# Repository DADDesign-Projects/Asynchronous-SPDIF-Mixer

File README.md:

# Asynchronous S/PDIF Mixer

"Asynchronous SPDIF Mixer" is a hardware and software project designed to synchronize and mix up to three asynchronous S/PDIF streams into a single 48 kHz output stream.  
The system compensates for drift between sources and uses interpolation to ensure smooth and artifact-free audio transitions.  
The project includes USB-MIDI control, allowing real-time mixing of the three audio channels via an external MIDI controller or any MIDI-compatible software.
  
The software, developed in C++ with CubeIDE, is optimized for real-time audio processing and runs on an STM32H743 microcontroller.  
A custom electronic board, designed with KiCad, provides a dedicated hardware platform for this solution.  

## 📋 New Evolutions

Recent updates to the project include:

- 🔄 **Enhanced Drift Compensation**: A new algorithm has been implemented for compensating drifts in the input frequencies, ensuring more precise synchronization across streams.
- 🎛️ **Advanced Mixing Controls**: Mixing between the three inputs can now be adjusted in real-time via MIDI over USB, complemented by a Python-based control panel for intuitive configuration. Mix settings are automatically saved and recalled as presets stored directly in flash memory for persistent, non-volatile access.

## 👤 Author

This project is developed by **DAD Design**.

## 📄 License

This project is licensed under the [MIT License](LICENSE).

## ✨ Features

- **Synchronization of Asynchronous S/PDIF Streams:** The project synchronizes three input audio streams, each potentially running at different sample rates ( 48kHz, 44.1kHz, 32kHz), into a unified output stream at 48kHz.
- **Clock Drift Compensation:** Drift between the input streams is handled through periodic drift factor recalculation, ensuring the output remains smooth and synchronized.
- 🎛️ **Real-Time Mixing Controls**: Adjustable mixing levels for the three inputs via any USB-MIDI interface. A Python control panel included as an example for easy configuration.
- 💾 **Preset Memorization**: Mix settings are automatically saved and can be recalled as presets stored in flash memory for quick, persistent access.

## 🛠️ Hardware Platform

The KiCAD folder contains the schematics and PCB files for the project's hardware. These files were created using **KiCAD version 9.0**.

## 🔧 Development Environment

The project is developed and compiled using the **CubeIDE** environment provided by STMicroelectronics. CubeIDE is a fully integrated development environment (IDE) that supports STM32 microcontrollers and provides tools for debugging, flashing, and developing embedded systems.

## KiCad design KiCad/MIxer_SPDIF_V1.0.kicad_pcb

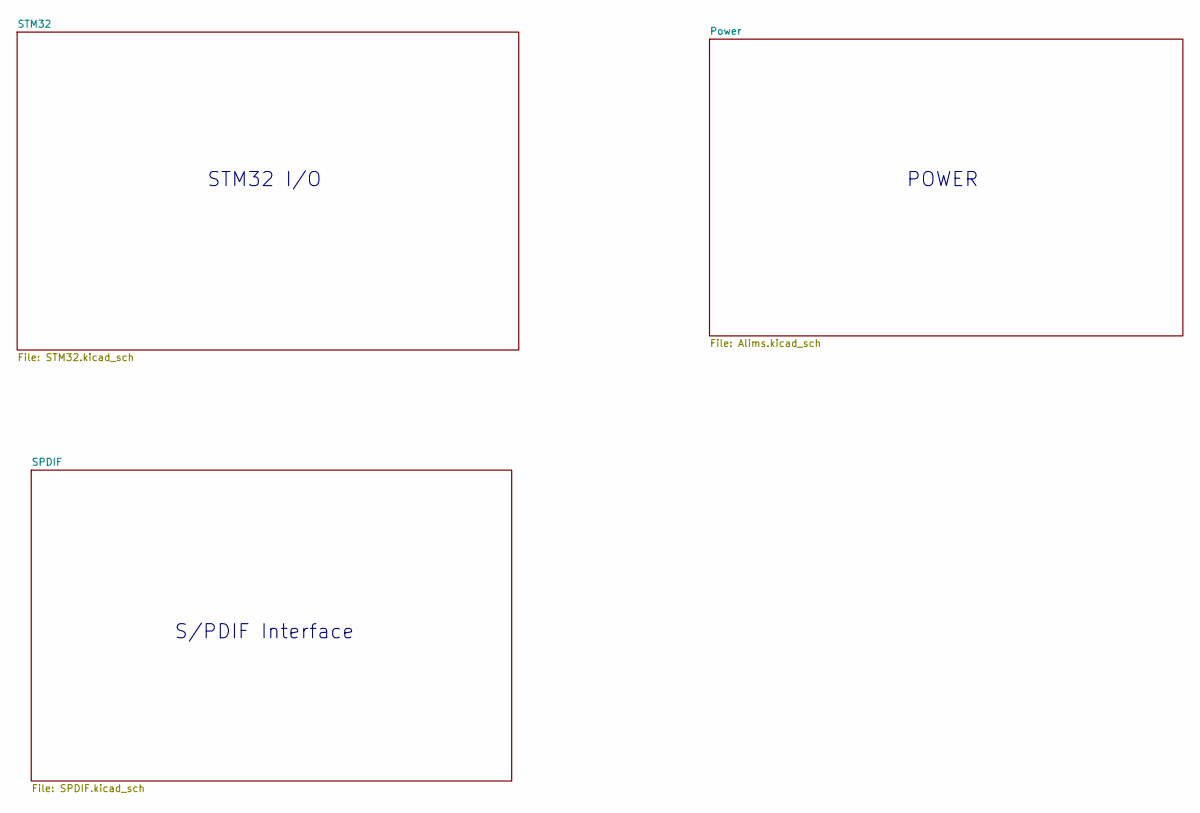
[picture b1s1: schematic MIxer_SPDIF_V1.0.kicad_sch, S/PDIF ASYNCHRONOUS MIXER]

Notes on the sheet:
POWER
S/PDIF Interface
STM32 I/O

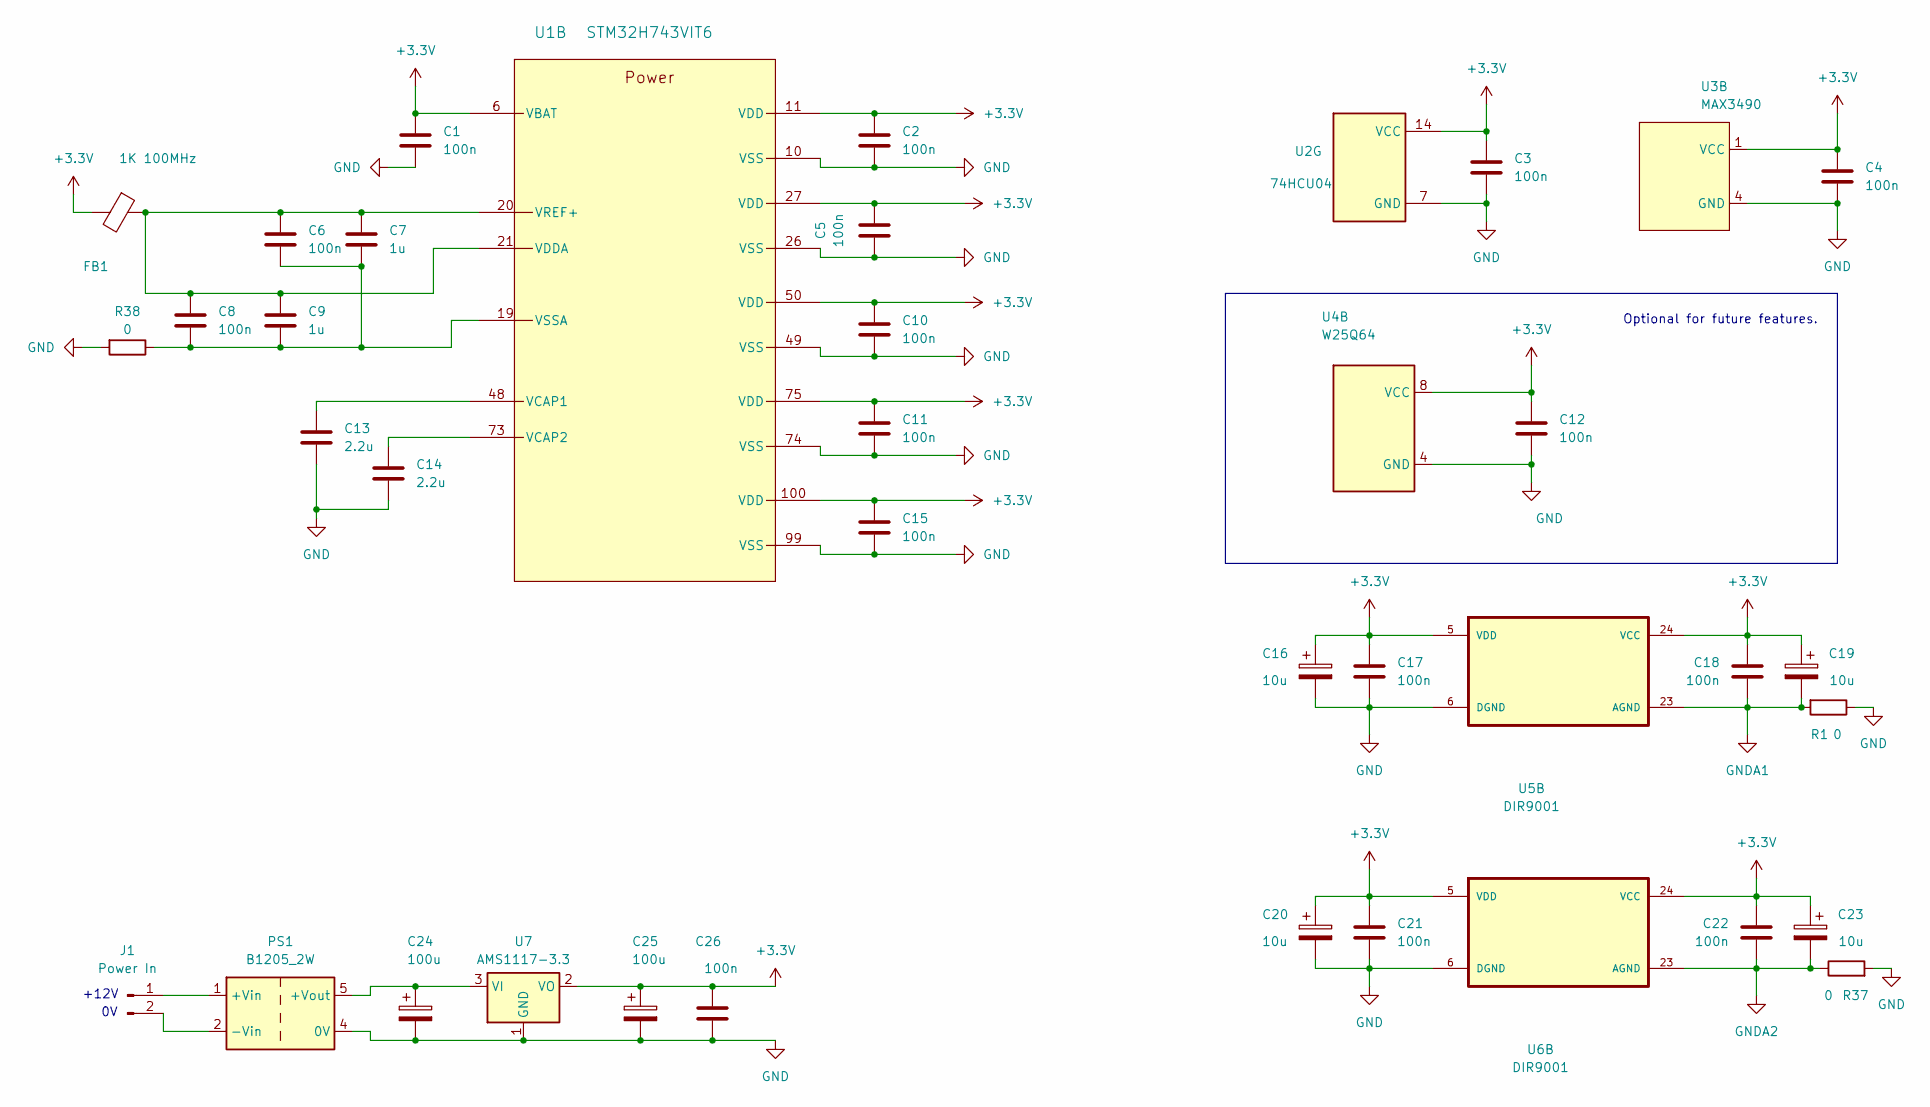
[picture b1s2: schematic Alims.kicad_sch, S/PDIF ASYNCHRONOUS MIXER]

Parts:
C1, C2, C3, C4, C5, C6, C8, C10, C11, C12, C15, C17, C18, C21, C22, C26: 100n; C_1206_3216Metric_Pad1.33x1.80mm_HandSolder
C7, C9: 1u; C_1206_3216Metric_Pad1.33x1.80mm_HandSolder
C13, C14: 2.2u; C_1206_3216Metric_Pad1.33x1.80mm_HandSolder
C16, C19, C20, C23: 10u; CP_Radial_D5.0mm_P2.50mm
C24, C25: 100u; CP_Radial_D6.3mm_P2.50mm
FB1: 1K 100MHz; C_0805_2012Metric_Pad1.18x1.45mm_HandSolder
J1: Power In; PinHeader_1x02_P2.54mm_Horizontal
PS1: B1205_2W; Converter_DCDC_TRACO_TBA1-xxxxE_Single_THT
R1, R37, R38: 0; SolderJumper-2_P1.3mm_Bridged2Bar_Pad1.0x1.5mm
U1: STM32H743VIT6; LQFP100-14x14mm
U2: 74HCU04; SO-14_5.3x10.2mm_P1.27mm
U3: MAX3490; SOIC-8_3.9x4.9mm_P1.27mm
U4: W25Q64; SOIC-8_5.23x5.23mm_P1.27mm
U5, U6: DIR9001; TSSOP-28-1EP_4.4x9.7mm_P0.65mm_EP2.85x6.7mm
U7: AMS1117-3.3; SOT-223-3_TabPin2

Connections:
+3.3V: C1.1, C2.1, C3.1, C4.1, C5.1, C10.1, C11.1, C12.1, C15.1, C16.1, C17.1, C18.1, C19.1, C20.1, C21.1, C22.1, C23.1, C25.1, C26.1, FB1.2, U1.6 (VBAT), U1.11 (VDD), U1.27 (VDD), U1.50 (VDD), U1.75 (VDD), U1.100 (VDD), U2.14 (VCC), U3.1 (VCC), U4.8 (VCC), U5.5 (VDD), U5.24 (VCC), U6.5 (VDD), U6.24 (VCC), U7.2 (VO); also elsewhere on the board
GND: C1.2, C2.2, C3.2, C4.2, C5.2, C10.2, C11.2, C12.2, C13.2, C14.2, C15.2, C16.2, C17.2, C20.2, C21.2, C24.2, C25.2, C26.2, PS1.4 (0V), R1.1, R37.2, R38.2, U1.10 (VSS), U1.26 (VSS), U1.49 (VSS), U1.74 (VSS), U1.99 (VSS), U2.7 (GND), U3.4 (GND), U4.4 (GND), U5.6 (DGND), U6.6 (DGND), U7.1 (GND); also elsewhere on the board
GNDA1: C18.2, C19.2, R1.2, U5.23 (AGND); also elsewhere on the board
GNDA2: C22.2, C23.2, R37.1, U6.23 (AGND); also elsewhere on the board
unnamed: J1.2 (0V), PS1.2 (-Vin)
unnamed: J1.1 (12V), PS1.1 (+Vin)
unnamed: C24.1, PS1.5 (+Vout), U7.3 (VI)
unnamed: C13.1, U1.48 (VCAP1)
unnamed: C14.1, U1.73 (VCAP2)
unnamed: C6.1, C7.1, C8.1, C9.1, FB1.1, U1.20 (VREF+), U1.21 (VDDA)
unnamed: C6.2, C7.2, C8.2, C9.2, R38.1, U1.19 (VSSA)

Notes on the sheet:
Optional for future features.
+12V

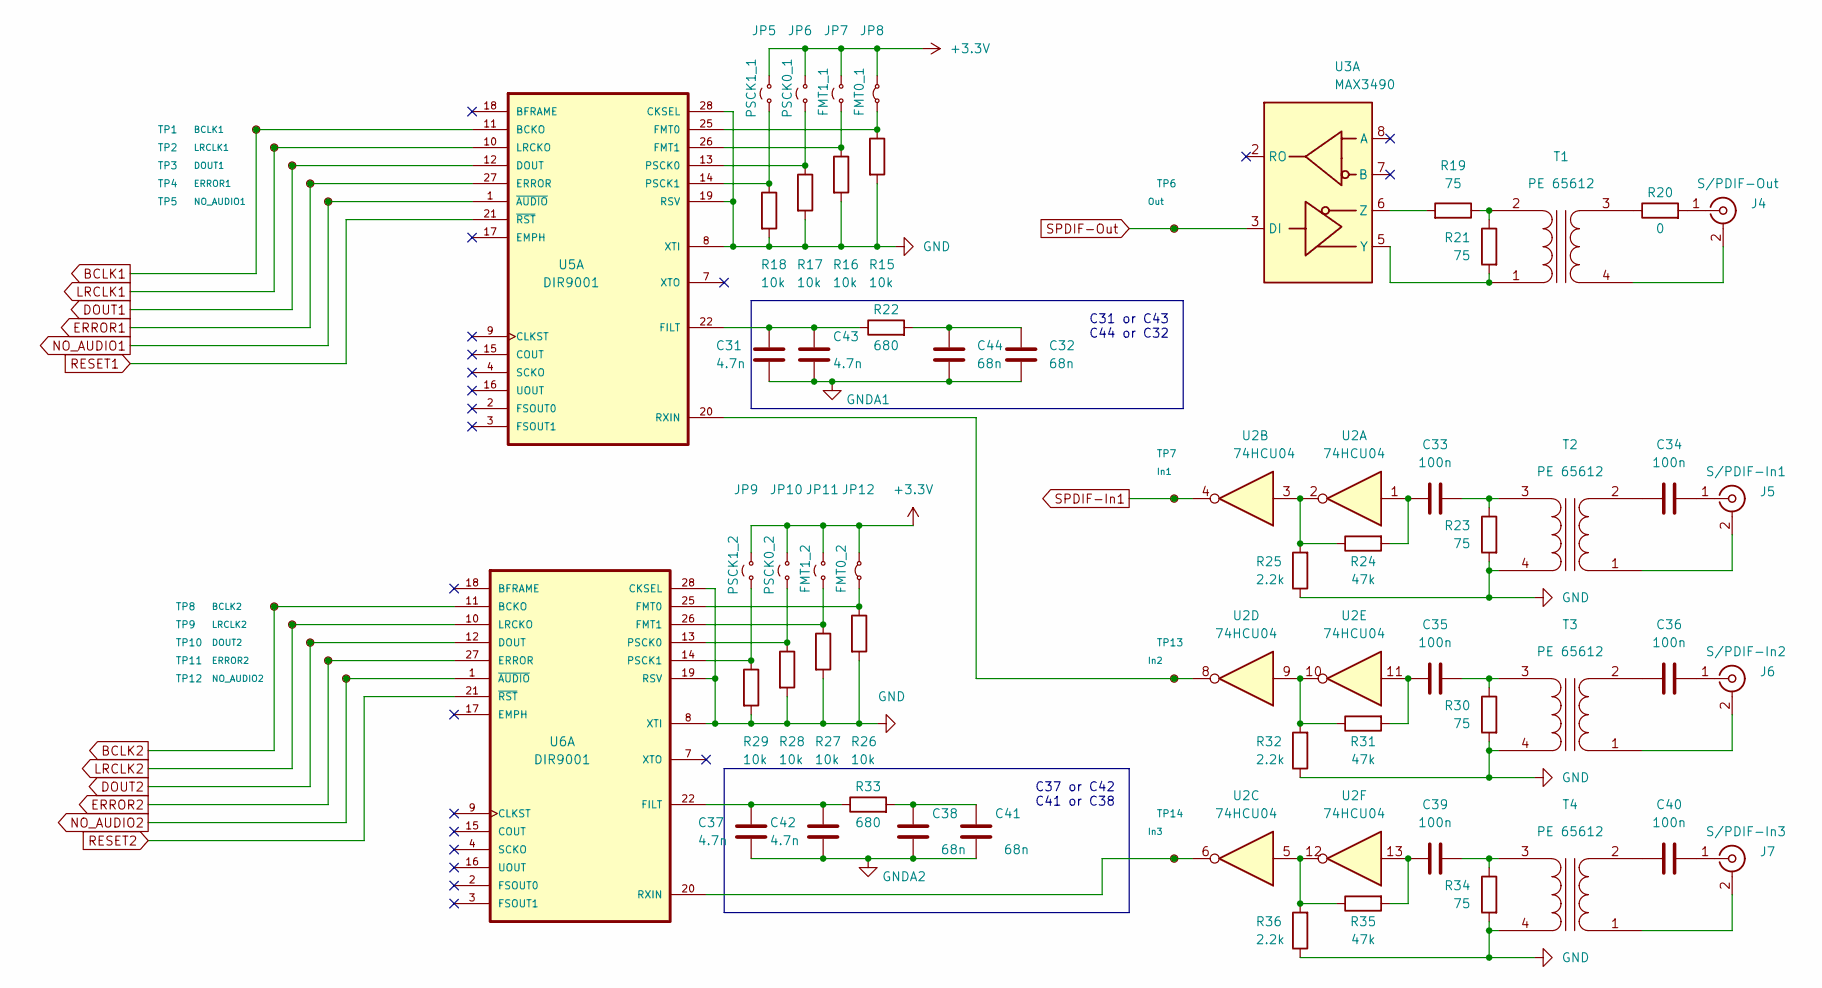
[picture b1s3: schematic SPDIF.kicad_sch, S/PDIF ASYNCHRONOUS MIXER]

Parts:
C31, C37: 4.7n; C_1206_3216Metric_Pad1.33x1.80mm_HandSolder
C32, C38: 68n; C_1206_3216Metric_Pad1.33x1.80mm_HandSolder
C33, C34, C35, C36, C39, C40: 100n; C_1206_3216Metric_Pad1.33x1.80mm_HandSolder
C41, C44: 68n; C_Rect_L4.6mm_W2.0mm_P2.50mm_MKS02_FKP02
C42, C43: 4.7n; C_Rect_L4.6mm_W2.0mm_P2.50mm_MKS02_FKP02
J4: S/PDIF-Out; CINCH_RCA
J5: S/PDIF-In1; CINCH_RCA
J6: S/PDIF-In2; CINCH_RCA
J7: S/PDIF-In3; CINCH_RCA
JP5: PSCK1_1; PinHeader_1x02_P2.54mm_Vertical
JP6: PSCK0_1; PinHeader_1x02_P2.54mm_Vertical
JP7: FMT1_1; PinHeader_1x02_P2.54mm_Vertical
JP8: FMT0_1; PinHeader_1x02_P2.54mm_Vertical
JP9: PSCK1_2; PinHeader_1x02_P2.54mm_Vertical
JP10: PSCK0_2; PinHeader_1x02_P2.54mm_Vertical
JP11: FMT1_2; PinHeader_1x02_P2.54mm_Vertical
JP12: FMT0_2; PinHeader_1x02_P2.54mm_Vertical
R15, R16, R17, R18, R26, R27, R28, R29: 10k; R_1206_3216Metric_Pad1.30x1.75mm_HandSolder
R19, R21, R23, R30, R34: 75; R_1206_3216Metric_Pad1.30x1.75mm_HandSolder
R20: 0; R_1206_3216Metric_Pad1.30x1.75mm_HandSolder
R22, R33: 680; R_1206_3216Metric_Pad1.30x1.75mm_HandSolder
R24, R31, R35: 47k; R_1206_3216Metric_Pad1.30x1.75mm_HandSolder
R25, R32, R36: 2.2k; R_1206_3216Metric_Pad1.30x1.75mm_HandSolder
T1, T2, T3, T4: PE 65612; PE-65612
TP1: BCLK1; TestPoint_THTPad_1.5x1.5mm_Drill0.7mm
TP2: LRCLK1; TestPoint_THTPad_1.5x1.5mm_Drill0.7mm
TP3: DOUT1; TestPoint_THTPad_1.5x1.5mm_Drill0.7mm
TP4: ERROR1; TestPoint_THTPad_1.5x1.5mm_Drill0.7mm
TP5: NO_AUDIO1; TestPoint_THTPad_1.5x1.5mm_Drill0.7mm
TP6: Out; TestPoint_THTPad_1.5x1.5mm_Drill0.7mm
TP7: In1; TestPoint_THTPad_1.5x1.5mm_Drill0.7mm
TP8: BCLK2; TestPoint_THTPad_1.5x1.5mm_Drill0.7mm
TP9: LRCLK2; TestPoint_THTPad_1.5x1.5mm_Drill0.7mm
TP10: DOUT2; TestPoint_THTPad_1.5x1.5mm_Drill0.7mm
TP11: ERROR2; TestPoint_THTPad_1.5x1.5mm_Drill0.7mm
TP12: NO_AUDIO2; TestPoint_THTPad_1.5x1.5mm_Drill0.7mm
TP13: In2; TestPoint_THTPad_1.5x1.5mm_Drill0.7mm
TP14: In3; TestPoint_THTPad_1.5x1.5mm_Drill0.7mm
U2: 74HCU04; SO-14_5.3x10.2mm_P1.27mm
U3: MAX3490; SOIC-8_3.9x4.9mm_P1.27mm
U5, U6: DIR9001; TSSOP-28-1EP_4.4x9.7mm_P0.65mm_EP2.85x6.7mm

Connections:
+3.3V: JP5.2 (B), JP6.2 (B), JP7.2 (B), JP8.2 (B), JP9.2 (B), JP10.2 (B), JP11.2 (B), JP12.2 (B); also elsewhere on the board
BCLK1: TP1.1, U5.11 (BCKO); also elsewhere on the board
BCLK2: TP8.1, U6.11 (BCKO); also elsewhere on the board
DOUT1: TP3.1, U5.12 (DOUT); also elsewhere on the board
DOUT2: TP10.1, U6.12 (DOUT); also elsewhere on the board
ERROR1: TP4.1, U5.27 (ERROR); also elsewhere on the board
ERROR2: TP11.1, U6.27 (ERROR); also elsewhere on the board
GND: R15.2, R16.2, R17.2, R18.2, R23.2, R25.1, R26.2, R27.2, R28.2, R29.2, R30.2, R32.1, R34.2, R36.1, T2.4 (SB), T3.4 (SB), T4.4 (SB), U5.8 (XTI), U5.19 (RSV), U5.28 (CKSEL), U6.8 (XTI), U6.19 (RSV), U6.28 (CKSEL); also elsewhere on the board
GNDA1: C31.2, C32.2, C43.2, C44.2; also elsewhere on the board
GNDA2: C37.2, C38.2, C41.2, C42.2; also elsewhere on the board
LRCLK1: TP2.1, U5.10 (LRCKO); also elsewhere on the board
LRCLK2: TP9.1, U6.10 (LRCKO); also elsewhere on the board
NO_AUDIO1: TP5.1, U5.1 (~AUDIO); also elsewhere on the board
NO_AUDIO2: TP12.1, U6.1 (~AUDIO); also elsewhere on the board
unnamed: C32.1, C44.1, R22.2
unnamed: C33.1, R24.2, U2.1
unnamed: C35.1, R31.2, U2.11
unnamed: C38.1, C41.1, R33.2
unnamed: C39.1, R35.2, U2.13
unnamed: J4.2 (Ext), T1.4 (SB)
unnamed: J4.1 (In), R20.2
unnamed: J5.2 (Ext), T2.1 (AA)
unnamed: C34.1, J5.1 (In)
unnamed: J6.2 (Ext), T3.1 (AA)
unnamed: C36.1, J6.1 (In)
unnamed: J7.2 (Ext), T4.1 (AA)
unnamed: C40.1, J7.1 (In)
unnamed: JP5.1 (A), R18.1, U5.14 (PSCK1)
unnamed: JP6.1 (A), R17.1, U5.13 (PSCK0)
unnamed: JP7.1 (A), R16.1, U5.26 (FMT1)
unnamed: JP8.1 (A), R15.1, U5.25 (FMT0)
unnamed: JP9.1 (A), R29.1, U6.14 (PSCK1)
unnamed: JP10.1 (A), R28.1, U6.13 (PSCK0)
unnamed: JP11.1 (A), R27.1, U6.26 (FMT1)
unnamed: JP12.1 (A), R26.1, U6.25 (FMT0)
unnamed: R24.1, R25.2, U2.2, U2.3
unnamed: R31.1, R32.2, U2.9, U2.10
unnamed: R35.1, R36.2, U2.5, U2.12
unnamed: R21.2, T1.1 (AA), U3.5 (Y)
unnamed: R19.1, R21.1, T1.2 (AB)
unnamed: R20.1, T1.3 (SA)
unnamed: C34.2, T2.2 (AB)
unnamed: C33.2, R23.1, T2.3 (SA)
unnamed: C36.2, T3.2 (AB)
unnamed: C35.2, R30.1, T3.3 (SA)
unnamed: C40.2, T4.2 (AB)
unnamed: C39.2, R34.1, T4.3 (SA)
unnamed: R19.2, U3.6 (Z)
unnamed: C31.1, C43.1, R22.1, U5.22 (FILT)
unnamed: TP13.1, U2.8, U5.20 (RXIN)
unnamed: C37.1, C42.1, R33.1, U6.22 (FILT)
unnamed: TP14.1, U2.6, U6.20 (RXIN)
RESET1: U5.21 (~RST); also elsewhere on the board
RESET2: U6.21 (~RST); also elsewhere on the board
SPDIF-In1: TP7.1, U2.4; also elsewhere on the board
SPDIF-Out: TP6.1, U3.3 (DI); also elsewhere on the board

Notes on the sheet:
C37 or C42 C41 or C38
C31 or C43 C44 or C32

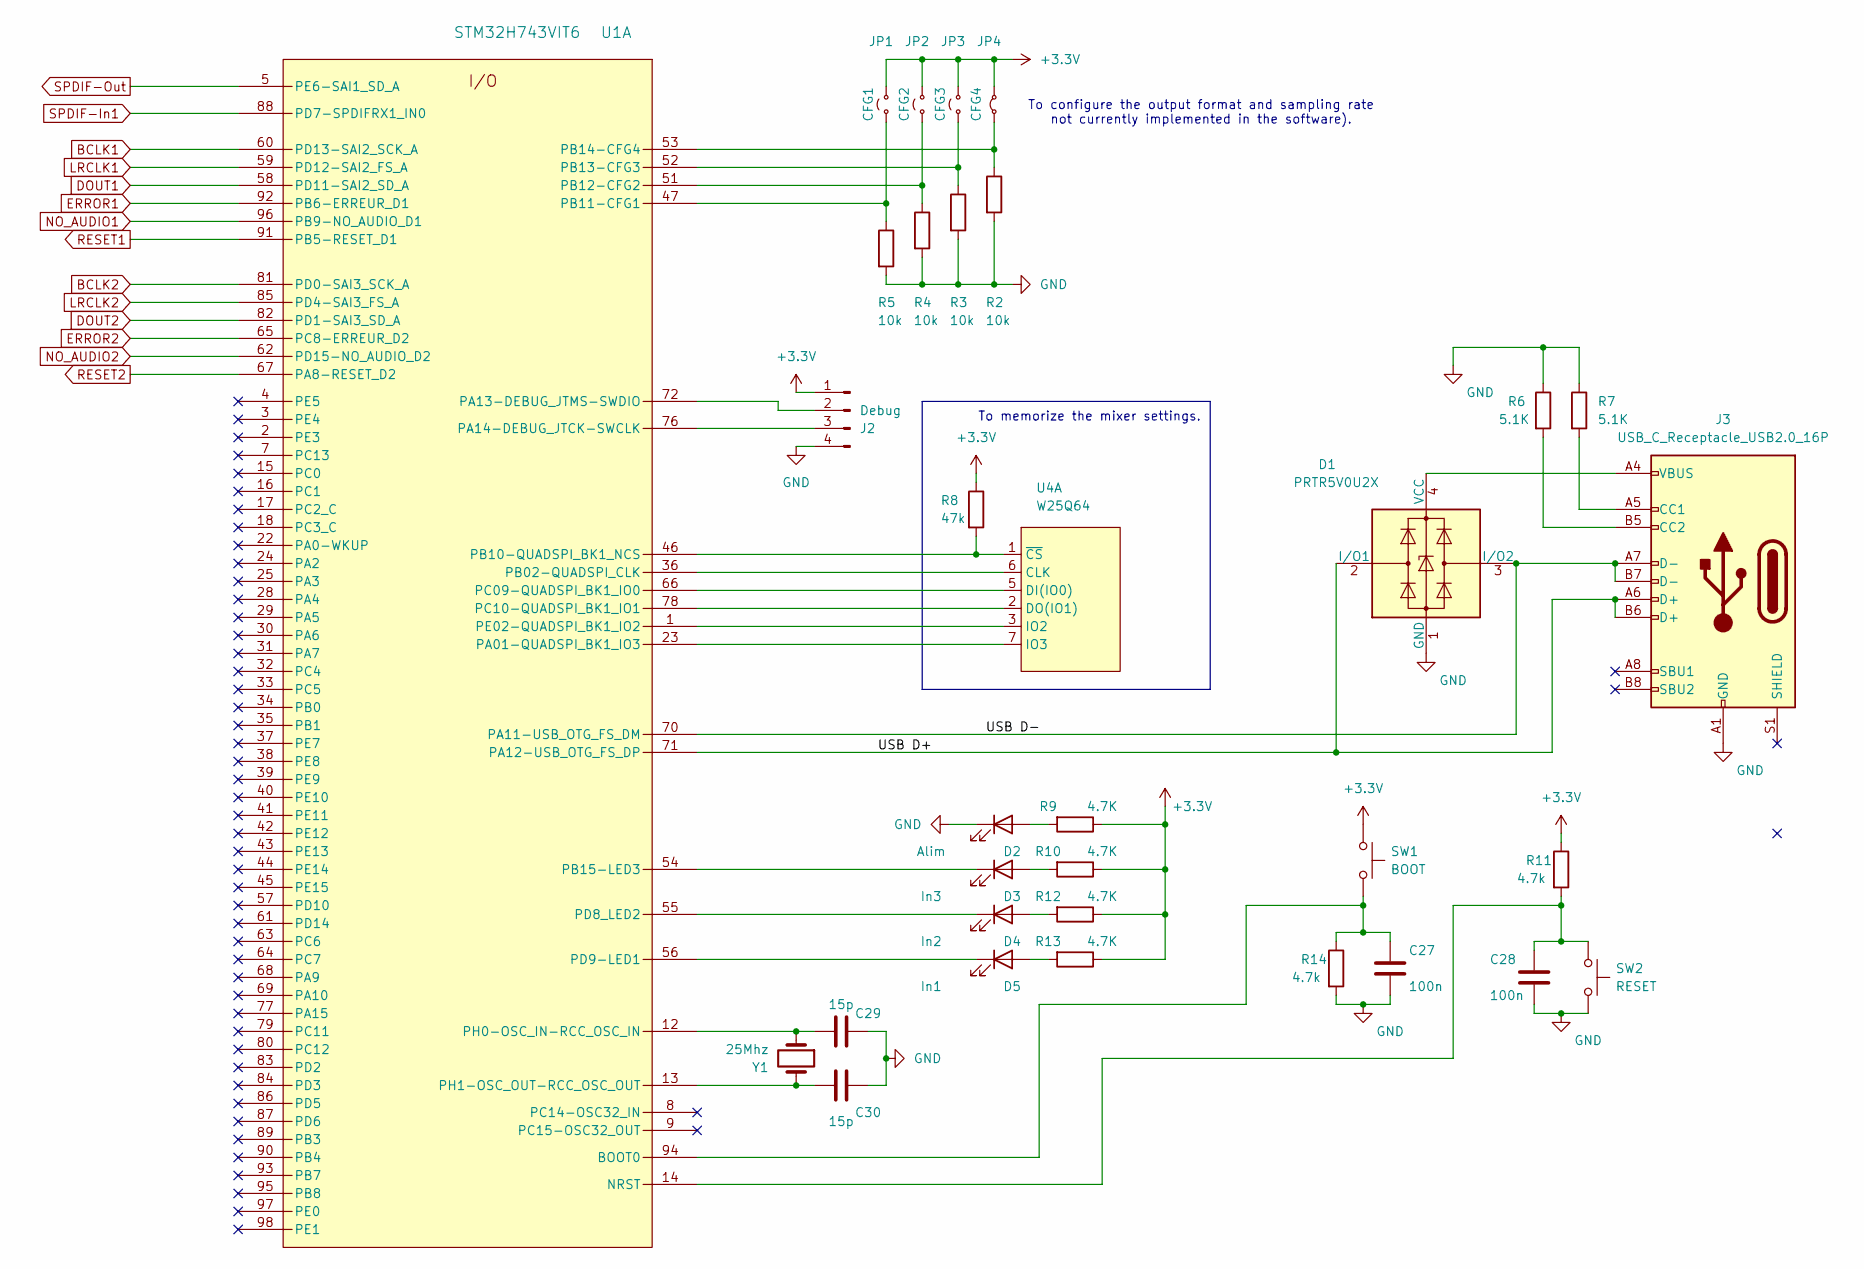
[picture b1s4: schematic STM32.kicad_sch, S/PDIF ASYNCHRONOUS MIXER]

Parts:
C27, C28: 100n; C_1206_3216Metric_Pad1.33x1.80mm_HandSolder
C29, C30: 15p; C_1206_3216Metric_Pad1.33x1.80mm_HandSolder
D1: PRTR5V0U2X; SOT-143
D2: Alim; LED_1206_3216Metric_Pad1.42x1.75mm_HandSolder
D3: In3; LED_1206_3216Metric_Pad1.42x1.75mm_HandSolder
D4: In2; LED_1206_3216Metric_Pad1.42x1.75mm_HandSolder
D5: In1; LED_1206_3216Metric_Pad1.42x1.75mm_HandSolder
J2: Debug; PinHeader_1x04_P2.54mm_Horizontal
J3: USB_C_Receptacle_USB2.0_16P; USB_C_Receptacle_HCTL_HC-TYPE-C-16P-01A
JP1: CFG1; PinHeader_1x02_P2.54mm_Vertical
JP2: CFG2; PinHeader_1x02_P2.54mm_Vertical
JP3: CFG3; PinHeader_1x02_P2.54mm_Vertical
JP4: CFG4; PinHeader_1x02_P2.54mm_Vertical
R2, R3, R4, R5: 10k; R_1206_3216Metric_Pad1.30x1.75mm_HandSolder
R6, R7: 5.1K; R_1206_3216Metric_Pad1.30x1.75mm_HandSolder
R8: 47k; R_1206_3216Metric_Pad1.30x1.75mm_HandSolder
R9, R10, R12, R13: 4.7K; R_1206_3216Metric_Pad1.30x1.75mm_HandSolder
R11, R14: 4.7k; R_1206_3216Metric_Pad1.30x1.75mm_HandSolder
SW1: BOOT; SW_PUSH_6mm_H5mm
SW2: RESET; SW_PUSH_6mm_H5mm
U1: STM32H743VIT6; LQFP100-14x14mm
U4: W25Q64; SOIC-8_5.23x5.23mm_P1.27mm
Y1: 25Mhz; Quartz

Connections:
+3.3V: J2.1, JP1.2 (B), JP2.2 (B), JP3.2 (B), JP4.2 (B), R8.1, R9.1, R10.1, R11.1, R12.1, R13.1, SW1.1; also elsewhere on the board
/STM32/USB D+: D1.2 (I/O1), J3.A6 (D+), J3.B6 (D+), U1.71 (PA12-USB_OTG_FS_DP)
/STM32/USB D-: D1.3 (I/O2), J3.A7 (D-), J3.B7 (D-), U1.70 (PA11-USB_OTG_FS_DM)
BCLK1: U1.60 (PD13-SAI2_SCK_A); also elsewhere on the board
BCLK2: U1.81 (PD0-SAI3_SCK_A); also elsewhere on the board
DOUT1: U1.58 (PD11-SAI2_SD_A); also elsewhere on the board
DOUT2: U1.82 (PD1-SAI3_SD_A); also elsewhere on the board
ERROR1: U1.92 (PB6-ERREUR_D1); also elsewhere on the board
ERROR2: U1.65 (PC8-ERREUR_D2); also elsewhere on the board
GND: C27.2, C28.2, C29.1, C30.1, D1.1 (GND), D2.1 (K), J2.4, J3.A1 (GND), J3.A12 (GND), J3.B1 (GND), J3.B12 (GND), R2.2, R3.2, R4.2, R5.2, R6.1, R7.1, R14.2, SW2.2; also elsewhere on the board
LRCLK1: U1.59 (PD12-SAI2_FS_A); also elsewhere on the board
LRCLK2: U1.85 (PD4-SAI3_FS_A); also elsewhere on the board
NO_AUDIO1: U1.96 (PB9-NO_AUDIO_D1); also elsewhere on the board
NO_AUDIO2: U1.62 (PD15-NO_AUDIO_D2); also elsewhere on the board
unnamed: D1.4 (VCC), J3.A4 (VBUS), J3.A9 (VBUS), J3.B4 (VBUS), J3.B9 (VBUS)
unnamed: D2.2 (A), R9.2
unnamed: D3.2 (A), R10.2
unnamed: D3.1 (K), U1.54 (PB15-LED3)
unnamed: D4.2 (A), R12.2
unnamed: D4.1 (K), U1.55 (PD8_LED2)
unnamed: D5.2 (A), R13.2
unnamed: D5.1 (K), U1.56 (PD9-LED1)
unnamed: J2.2, U1.72 (PA13-DEBUG_JTMS-SWDIO)
unnamed: J2.3, U1.76 (PA14-DEBUG_JTCK-SWCLK)
unnamed: J3.A5 (CC1), R7.2
unnamed: J3.B5 (CC2), R6.2
unnamed: JP1.1 (A), R5.1, U1.47 (PB11-CFG1)
unnamed: JP2.1 (A), R4.1, U1.51 (PB12-CFG2)
unnamed: JP3.1 (A), R3.1, U1.52 (PB13-CFG3)
unnamed: JP4.1 (A), R2.1, U1.53 (PB14-CFG4)
unnamed: C27.1, R14.1, SW1.2, U1.94 (BOOT0)
unnamed: C28.1, R11.2, SW2.1, U1.14 (NRST)
unnamed: U1.23 (PA01-QUADSPI_BK1_IO3), U4.7 (IO3)
unnamed: U1.36 (PB02-QUADSPI_CLK), U4.6 (CLK)
unnamed: R8.2, U1.46 (PB10-QUADSPI_BK1_NCS), U4.1 (~CS)
unnamed: U1.66 (PC09-QUADSPI_BK1_IO0), U4.5 (DI(IO0))
unnamed: U1.78 (PC10-QUADSPI_BK1_IO1), U4.2 (DO(IO1))
unnamed: U1.1 (PE02-QUADSPI_BK1_IO2), U4.3 (IO2)
unnamed: C29.2, U1.12 (PH0-OSC_IN-RCC_OSC_IN), Y1.1
unnamed: C30.2, U1.13 (PH1-OSC_OUT-RCC_OSC_OUT), Y1.2
RESET1: U1.91 (PB5-RESET_D1); also elsewhere on the board
RESET2: U1.67 (PA8-RESET_D2); also elsewhere on the board
SPDIF-In1: U1.88 (PD7-SPDIFRX1_IN0); also elsewhere on the board
SPDIF-Out: U1.5 (PE6-SAI1_SD_A); also elsewhere on the board

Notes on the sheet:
To configure the output format and sampling rate not currently implemented in the software).
To memorize the mixer settings.

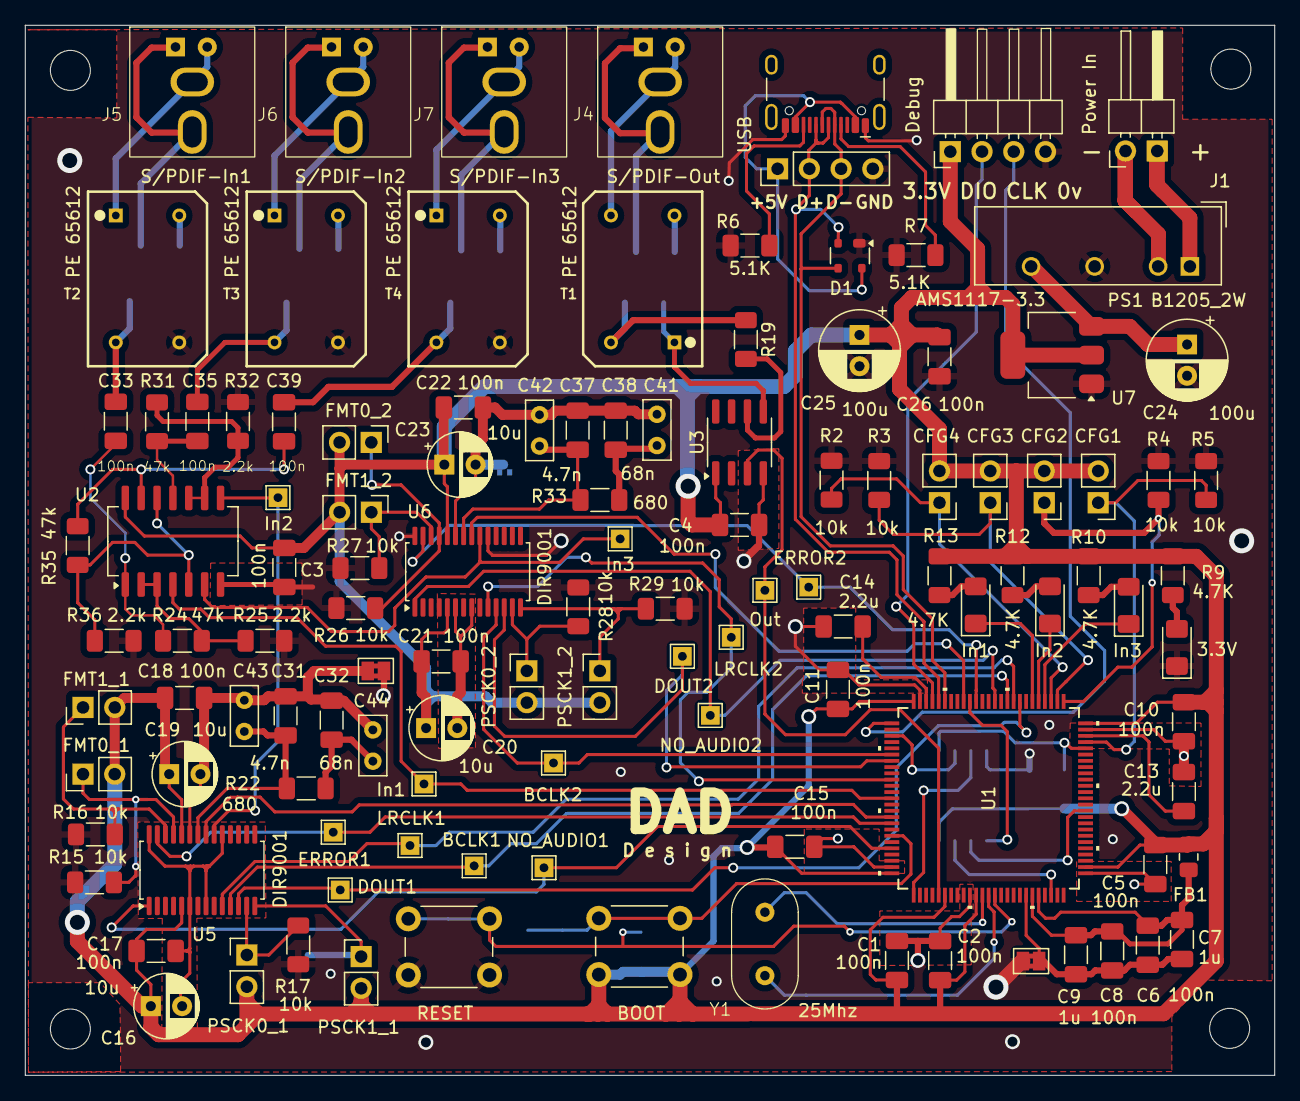
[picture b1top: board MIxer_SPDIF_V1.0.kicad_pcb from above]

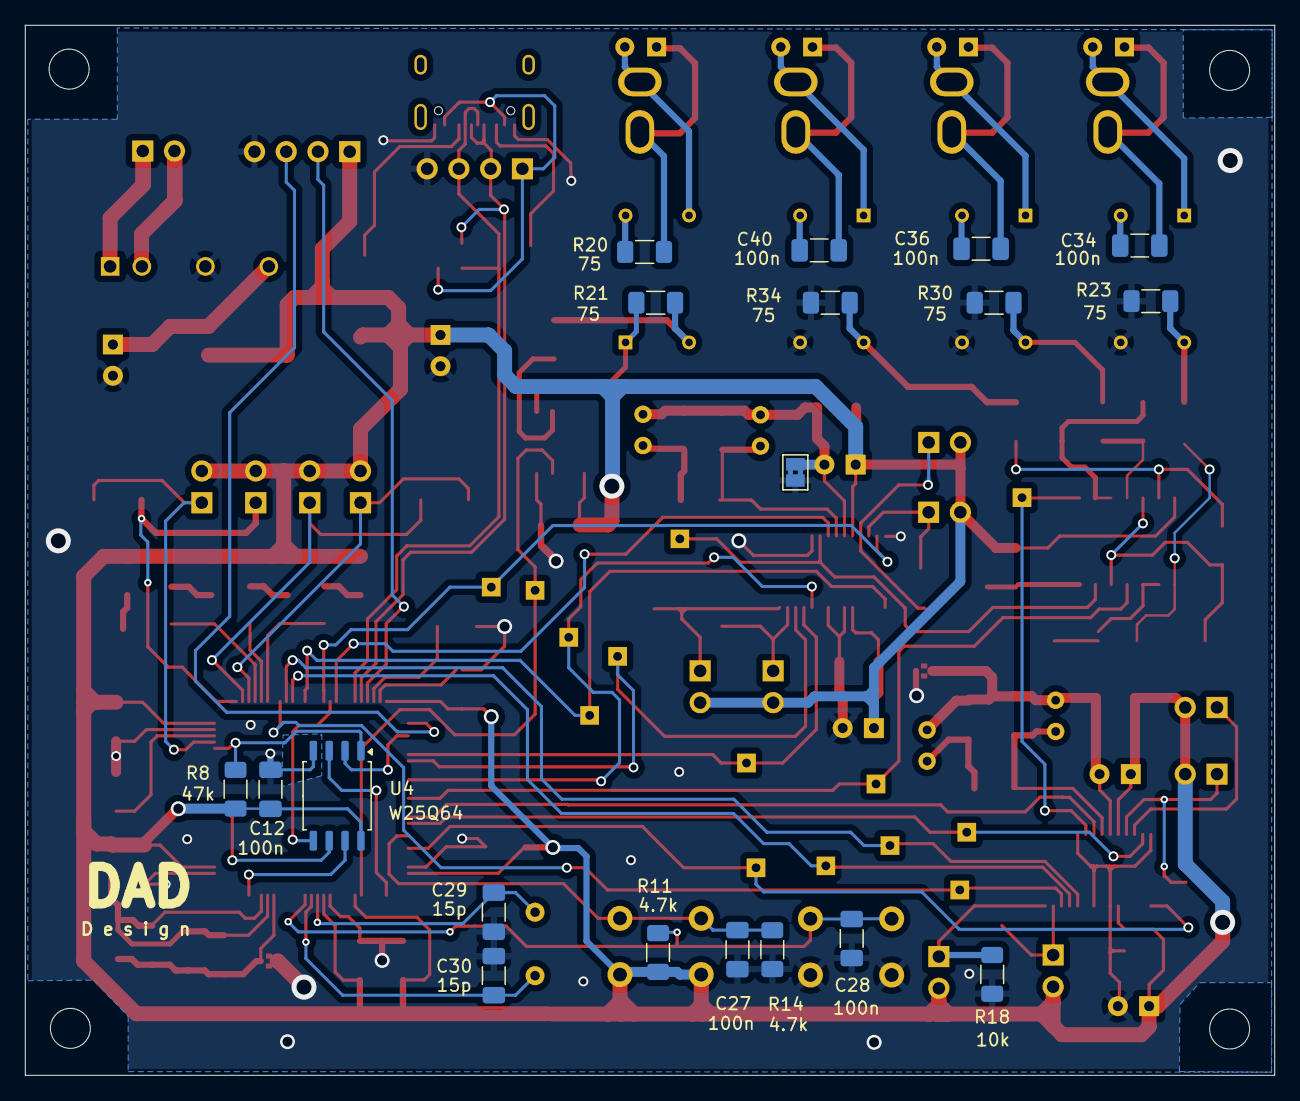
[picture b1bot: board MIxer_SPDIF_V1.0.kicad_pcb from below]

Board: 2 copper layers, 100.0 x 84.0 mm, 136 parts (19 on the bottom side), 91 nets.

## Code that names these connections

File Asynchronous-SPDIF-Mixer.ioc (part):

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Mcu.Name=STM32H743VITx
Mcu.Package=LQFP100
Mcu.UserName=STM32H743VITx
PA1.Mode=Single Bank 1
PA1.Signal=QUADSPI_BK1_IO3
PA11.GPIOParameters=GPIO_Speed
PA11.GPIO_Speed=GPIO_SPEED_FREQ_VERY_HIGH
PA11.Mode=Device_Only
PA11.Signal=USB_OTG_FS_DM
PA12.GPIOParameters=GPIO_Speed
PA12.GPIO_Speed=GPIO_SPEED_FREQ_VERY_HIGH
PA12.Mode=Device_Only
PA12.Signal=USB_OTG_FS_DP
PA13\ (JTMS/SWDIO).Mode=Serial_Wire
PA13\ (JTMS/SWDIO).Signal=DEBUG_JTMS-SWDIO
PA14\ (JTCK/SWCLK).Mode=Serial_Wire
PA14\ (JTCK/SWCLK).Signal=DEBUG_JTCK-SWCLK
PA8.GPIOParameters=GPIO_Label
PA8.GPIO_Label=RESET2
PA8.Signal=GPIO_Output
PB10.Mode=Single Bank 1
PB10.Signal=QUADSPI_BK1_NCS
PB12.GPIOParameters=GPIO_Label
PB12.GPIO_Label=EN_D1
PB12.Signal=GPIO_Input
PB13.GPIOParameters=GPIO_Label
PB13.GPIO_Label=EN_D2
PB13.Signal=GPIO_Input
PB14.GPIOParameters=GPIO_Label
PB14.GPIO_Label=EN_D3
PB14.Signal=GPIO_Input
PB15.GPIOParameters=PinState,GPIO_PuPd,GPIO_Label,GPIO_ModeDefaultOutputPP
PB15.GPIO_Label=LED3
PB15.GPIO_ModeDefaultOutputPP=GPIO_MODE_OUTPUT_OD
PB15.GPIO_PuPd=GPIO_NOPULL
PB15.PinState=GPIO_PIN_SET
PB15.Signal=GPIO_Output
PB2.Mode=Single Bank 1
PB2.Signal=QUADSPI_CLK
PB5.GPIOParameters=GPIO_Label
PB5.GPIO_Label=RESET1
PB5.Signal=GPIO_Output
PB6.GPIOParameters=GPIO_Label
PB6.GPIO_Label=ERROR1
PB6.Signal=GPIO_Input
PB9.GPIOParameters=GPIO_Label
PB9.GPIO_Label=NO_AUDIO1
PB9.Signal=GPIO_Input
PC10.Mode=Single Bank 1
PC10.Signal=QUADSPI_BK1_IO1
PC8.GPIOParameters=GPIO_Label
PC8.GPIO_Label=ERROR2
PC8.Signal=GPIO_Input
PC9.Mode=Single Bank 1
PC9.Signal=QUADSPI_BK1_IO0
PD0.GPIOParameters=GPIO_Speed
PD0.GPIO_Speed=GPIO_SPEED_FREQ_VERY_HIGH
PD0.Mode=SAI_A_AsyncSlave
PD0.Signal=SAI3_SCK_A
PD1.GPIOParameters=GPIO_Speed
PD1.GPIO_Speed=GPIO_SPEED_FREQ_VERY_HIGH
PD1.Mode=SAI_A_AsyncSlave
PD1.Signal=SAI3_SD_A
PD11.GPIOParameters=GPIO_Speed
PD11.GPIO_Speed=GPIO_SPEED_FREQ_VERY_HIGH
PD11.Mode=SAI_A_AsyncSlave
PD11.Signal=SAI2_SD_A
PD12.GPIOParameters=GPIO_Speed
PD12.GPIO_Speed=GPIO_SPEED_FREQ_VERY_HIGH
PD12.Mode=SAI_A_AsyncSlave
PD12.Signal=SAI2_FS_A
PD13.GPIOParameters=GPIO_Speed
PD13.GPIO_Speed=GPIO_SPEED_FREQ_VERY_HIGH
PD13.Mode=SAI_A_AsyncSlave
PD13.Signal=SAI2_SCK_A
PD15.GPIOParameters=GPIO_Label
PD15.GPIO_Label=NO_AUDIO2
PD15.Signal=GPIO_Input
PD4.GPIOParameters=GPIO_Speed
PD4.GPIO_Speed=GPIO_SPEED_FREQ_VERY_HIGH
PD4.Mode=SAI_A_AsyncSlave
PD4.Signal=SAI3_FS_A
PD7.GPIOParameters=GPIO_Speed
PD7.GPIO_Speed=GPIO_SPEED_FREQ_VERY_HIGH
PD7.Mode=IN0
PD7.Signal=SPDIFRX1_IN0
PD8.GPIOParameters=PinState,GPIO_PuPd,GPIO_Label,GPIO_ModeDefaultOutputPP
PD8.GPIO_Label=LED2
PD8.GPIO_ModeDefaultOutputPP=GPIO_MODE_OUTPUT_OD
PD8.GPIO_PuPd=GPIO_NOPULL
PD8.PinState=GPIO_PIN_SET
PD8.Signal=GPIO_Output
PD9.GPIOParameters=PinState,GPIO_PuPd,GPIO_Label,GPIO_ModeDefaultOutputPP
PD9.GPIO_Label=LED1
PD9.GPIO_ModeDefaultOutputPP=GPIO_MODE_OUTPUT_OD
PD9.GPIO_PuPd=GPIO_NOPULL
PD9.PinState=GPIO_PIN_SET
PD9.Signal=GPIO_Output
PE2.Mode=Single Bank 1
PE2.Signal=QUADSPI_BK1_IO2
PE6.GPIOParameters=GPIO_Speed
PE6.GPIO_Speed=GPIO_SPEED_FREQ_VERY_HIGH
PE6.Mode=SAI_A_SPDIF
PE6.Signal=SAI1_SD_A
PH0-OSC_IN\ (PH0).Mode=HSE-External-Oscillator
PH0-OSC_IN\ (PH0).Signal=RCC_OSC_IN
PH1-OSC_OUT\ (PH1).Mode=HSE-External-Oscillator
PH1-OSC_OUT\ (PH1).Signal=RCC_OSC_OUT
RCC.SYSCLKFreq_VALUE=480000000
RCC.SYSCLKSource=RCC_SYSCLKSOURCE_PLLCLK
board=custom

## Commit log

2024-09-27 First
2024-10-01 Rename Project.ioc
2024-10-09 Device Handler Redesign
2024-10-20 Change for DIR9001
    Change WM8805 for DIR9001
2024-10-24 improvement in behavior during frequency changes.
2024-11-30 Add PCB
2024-11-30 Image
2024-12-01 minor fixes
2024-12-04 Add image
2024-12-04 Adjustment of clocks.
    Adjustment of clocks: Switch to quartz and fine-tuning of the output sampling rate.
2024-12-04 Reduction of the drift correction factor.
    Reduction of the drift correction factor to accommodate less precise devices.
2025-02-05 stupid float conversion bug fix
2025-12-02 Minor and non-functional changes migration to KiCad 9
2025-12-02 Redesign of the drift compensation algorithm; addition of mixing for the 3 SPDIF channels via MIDI over USB.
2025-12-02 Revise README for clarity and feature updates
    Updated project description and features for clarity and accuracy. Changed version references and improved language for better readability.
